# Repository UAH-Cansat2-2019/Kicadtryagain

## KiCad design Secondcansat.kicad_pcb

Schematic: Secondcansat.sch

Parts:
C1, C5: 10uF; C_1206_3216Metric_Pad1.42x1.75mm_HandSolder
C2, C4, C10, C12: 100nF; C_0603_1608Metric_Pad1.05x0.95mm_HandSolder
C3, C14: 5uF; C_0603_1608Metric_Pad1.05x0.95mm_HandSolder
C6: 10uF; C_0805_2012Metric_Pad1.15x1.40mm_HandSolder
C7, C8, C11: 1uF; C_0603_1608Metric_Pad1.05x0.95mm_HandSolder
C9: 50uF; C_1206_3216Metric_Pad1.42x1.75mm_HandSolder
C13: 4.7uF; C_0603_1608Metric_Pad1.05x0.95mm_HandSolder
IC1: XBP9B-XCWT-001; XBP9BXCWT001_2; Mouser Part Number 888-XBP9B-XCWT-001
IMU1: BN0055breakout; BNO055breakout
J1: OpenlogBreakout; PinSocket_1x06_P2.54mm_Vertical
J2: Camera; PinSocket_1x03_P2.54mm_Vertical
J3: Pressure_MS5607; MS5607
J4: Debugger; PinSocket_2x03_P1.27mm_Vertical
J5: SFH_7776_OSRAM; PinSocket_2x04_P2.00mm_Vertical
J6: CAM-M8Q-GPS; CAM-M8Q
J7: GND; PinSocket_1x01_P2.54mm_Vertical
J8: SCL; PinSocket_1x01_P2.54mm_Vertical
J9: 3v; PinSocket_1x01_P2.54mm_Vertical
J10: SDA; PinSocket_1x01_P2.54mm_Vertical
J11: 5V; PinSocket_1x01_P2.54mm_Vertical
J12: Tx; PinSocket_1x01_P2.54mm_Vertical
J13: Rx; PinSocket_1x01_P2.54mm_Vertical
J14: Battery_Holder_keystone 1079; BatteryHolder
L1, L2: 10uH; L_0805_2012Metric_Pad1.15x1.40mm_HandSolder
MCU1: ATxmega128A4U-AU; ATXMEGA128A4U-AU
Moter1, Moter2: Moter_Adafruit_711; PinHeader_2x01_P2.54mm_Vertical
Q1: Q_PMOS_DMG2305UX-13DIDKR-ND; SOT-23
Q2, Q3, Q4: Q_NMOS_BSS138; SOT-23
R1: 274kohm; R_1206_3216Metric
R2: 30Kohm; R_0805_2012Metric_Pad1.15x1.40mm_HandSolder
R3, R4, R5, R6, R7, R11, R12, R13, R14, R15, R16, R17, R20: 10kohm; R_0603_1608Metric_Pad1.05x0.95mm_HandSolder
R8, R10: 2kohm; C_0805_2012Metric
R9: 5kohm; C_0805_2012Metric
R18, R19: 220ohm; R_0603_1608Metric_Pad1.05x0.95mm_HandSolder
Servo1: Servo_Adafruit_1142; PinSocket_1x03_P2.54mm_Vertical
TH1: Therm_NXRT15WB473FA3A016; PinSocket_2x01_P2.54mm_Vertical
U1: VR_TPS7A7001DDAR
U2, U3: H-bridge_MP6513GJ-P; H-Bridge_MP6513GJ-P
VR1: VR__TLV75533PDBVR; VR_296-50411-1-ND
buzzer1: buzzer_MAS803Q; PinSocket_1x02_P2.54mm_Vertical

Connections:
+3V3: C8.2, C9.2, C10.1, C11.1, C14.2, IC1.1, IMU1.1, J1.3, J3.1, J4.2, J5.1, J6.1, J6.9, J9.1, L2.1, R8.2, R11.1, R14.1, R15.1, R16.1, VR1.5
+5V: C6.1, C7.1, J2.2, J11.1, R1.1, R5.1, Servo1.2, U1.6, VR1.1, VR1.3; also elsewhere on the board
+6V: C3.1, Q1.3, R9.2, R17.2, U1.3, U2.5, U3.5, buzzer1.2
ADC_A1: MCU1.41 (PA1), R9.1, R10.2
CSB: J3.4, MCU1.14 (PC4)
GND: C1.2, C2.1, C3.2, C4.1, C5.2, C6.2, C7.2, C8.1, C9.1, C10.2, C11.2, C14.1, IC1.10, IMU1.3, IMU1.6, IMU1.10, J1.1, J1.2, J2.3, J3.2, J3.3, J4.6, J6.4, J6.5, J6.10, J6.11, J6.12, J6.13, J6.14, J6.15, J6.18, J6.19, J6.21, J6.22, J6.27, J6.31, J7.1, J14.3, MCU1.8 (GND), MCU1.18 (GND), MCU1.30 (GND), MCU1.38 (GND), Q1.2, Q2.3, Q3.3, Q4.3, R2.2, R3.2, R4.2, R6.2, R7.1, R10.1, R12.2, R13.2, R20.1, Servo1.1, TH1.1, U1.8, U2.2, U3.2, VR1.2; also elsewhere on the board
INT: J5.7, MCU1.33 (PE3), R14.2
MCUAVCC: C1.1, C2.2, L1.1, MCU1.39 (AVCC)
MCUVCC: C4.2, C5.1, L1.2, L2.2, MCU1.9 (VCC), MCU1.19 (VCC), MCU1.31 (VCC)
MISO: J3.6, MCU1.16 (PC6)
MOSI: J3.7, MCU1.15 (PC5)
MoterRIN1: MCU1.5 (PB1), R3.1, U2.1
MoterRIN2: MCU1.1 (PA5), R12.1, U3.1
MotorFIN1: MCU1.4 (AREFB/PB0), R4.1, U2.3
MotorFIN2: MCU1.44 (PA4), R13.1, U3.3
unnamed: C12.1, C13.1, J5.4
unnamed: C12.2, C13.2, J5.3
unnamed: J2.1, Q4.1
unnamed: J5.5, J5.6
unnamed: J6.16, J6.17
unnamed: J6.25, R18.1
unnamed: J6.26, R19.1
unnamed: J14.1, J14.2
unnamed: J14.4, Q1.1
unnamed 61: J6.8; also elsewhere on the board
unnamed: Moter1.1, U2.6
unnamed: Moter1.2, U2.4
unnamed: Moter2.1, U3.6
unnamed: Moter2.2, U3.4
unnamed: Q2.1, R5.2, Servo1.3
unnamed: Q3.1, buzzer1.1
unnamed: R1.2, R2.1, U1.7
unnamed: R17.1, U1.2
PDICLK: J4.5, MCU1.35 (~RESET~/PDI_CLK), R11.2
PDIDATA: J4.1, MCU1.34 (PDI_DATA)
PWM: MCU1.28 (PE0), Q2.2, R6.1
RX_PD2: IC1.2, MCU1.22 (PD2)
RX_PD6: J13.1, MCU1.26 (PD6), R18.2
SCL: IMU1.5, J5.2, J8.1, MCU1.11 (PC1), R16.2
SCLK: J3.8, MCU1.17 (PC7)
SDA: IMU1.4, J5.8, J10.1, MCU1.10 (PC0), R15.2
TC_PD0: MCU1.20 (PD0), Q3.2, R7.2
TX_PD3: IC1.3, MCU1.23 (PD3)
TX_PD7: J12.1, MCU1.27 (PD7), R19.2
Therm_ADCA0: MCU1.40 (AREFA/PA0), R8.1, TH1.2
USART_RX_PC2: J1.4, MCU1.12 (PC2)
USART_TX_PC3: J1.5, MCU1.13 (PC3)
cameraon: MCU1.32 (PE2), Q4.2, R20.2

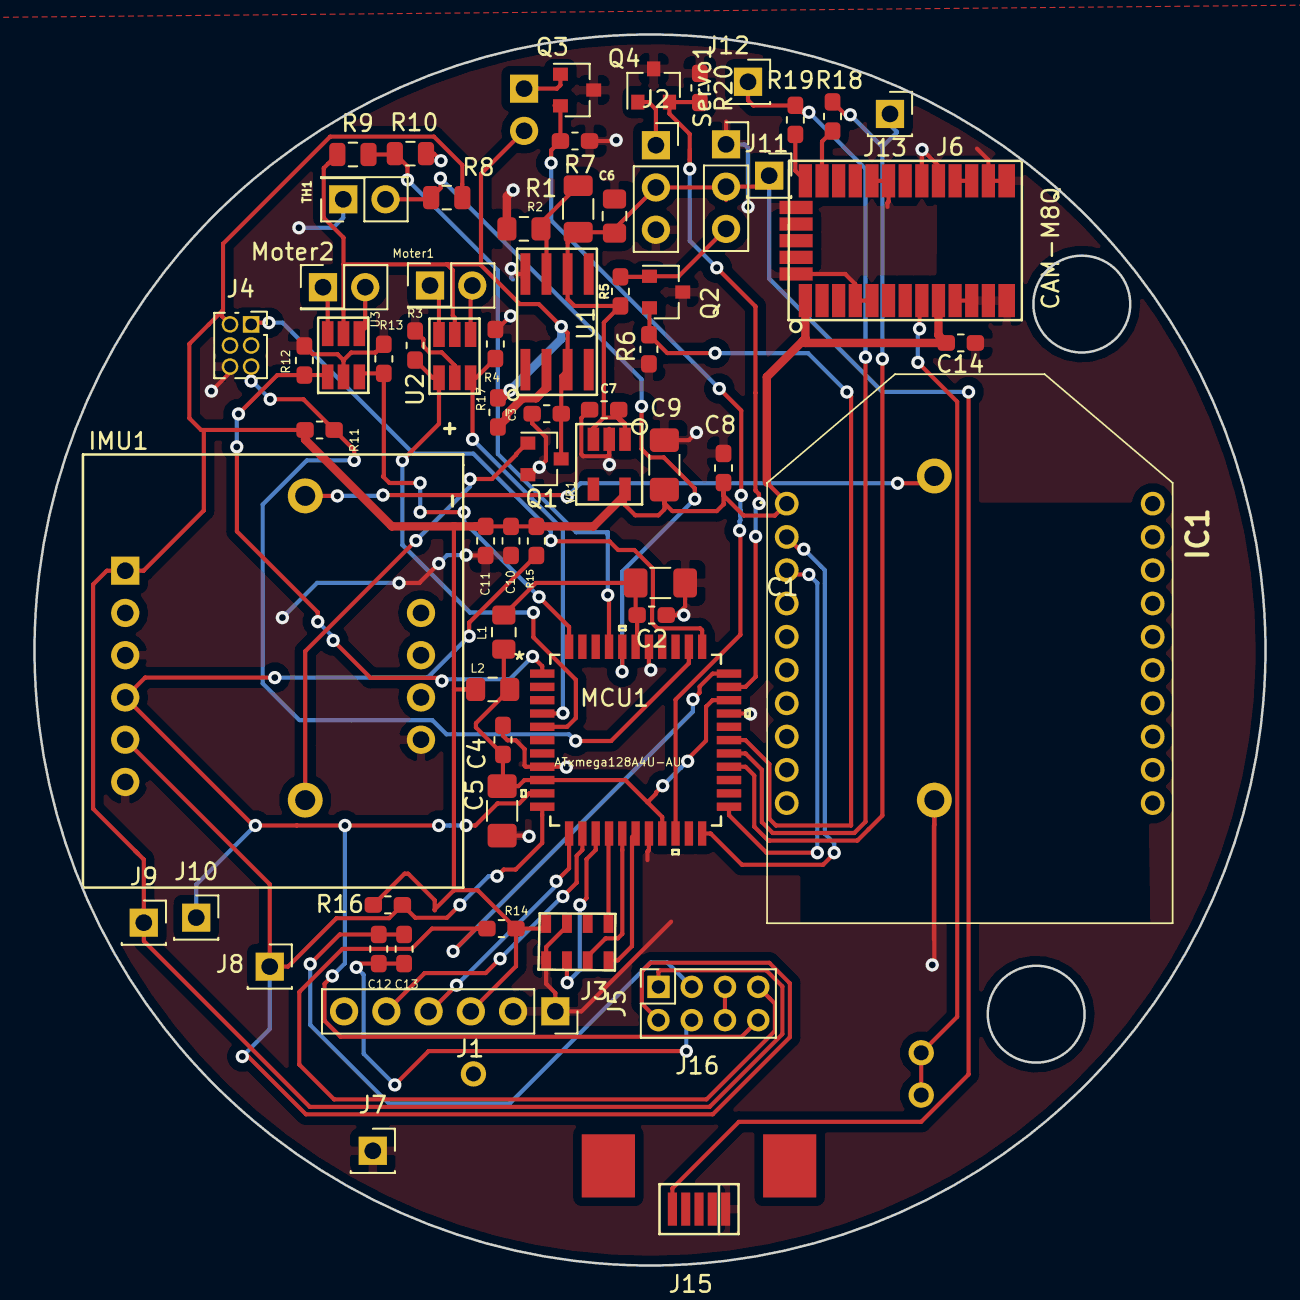
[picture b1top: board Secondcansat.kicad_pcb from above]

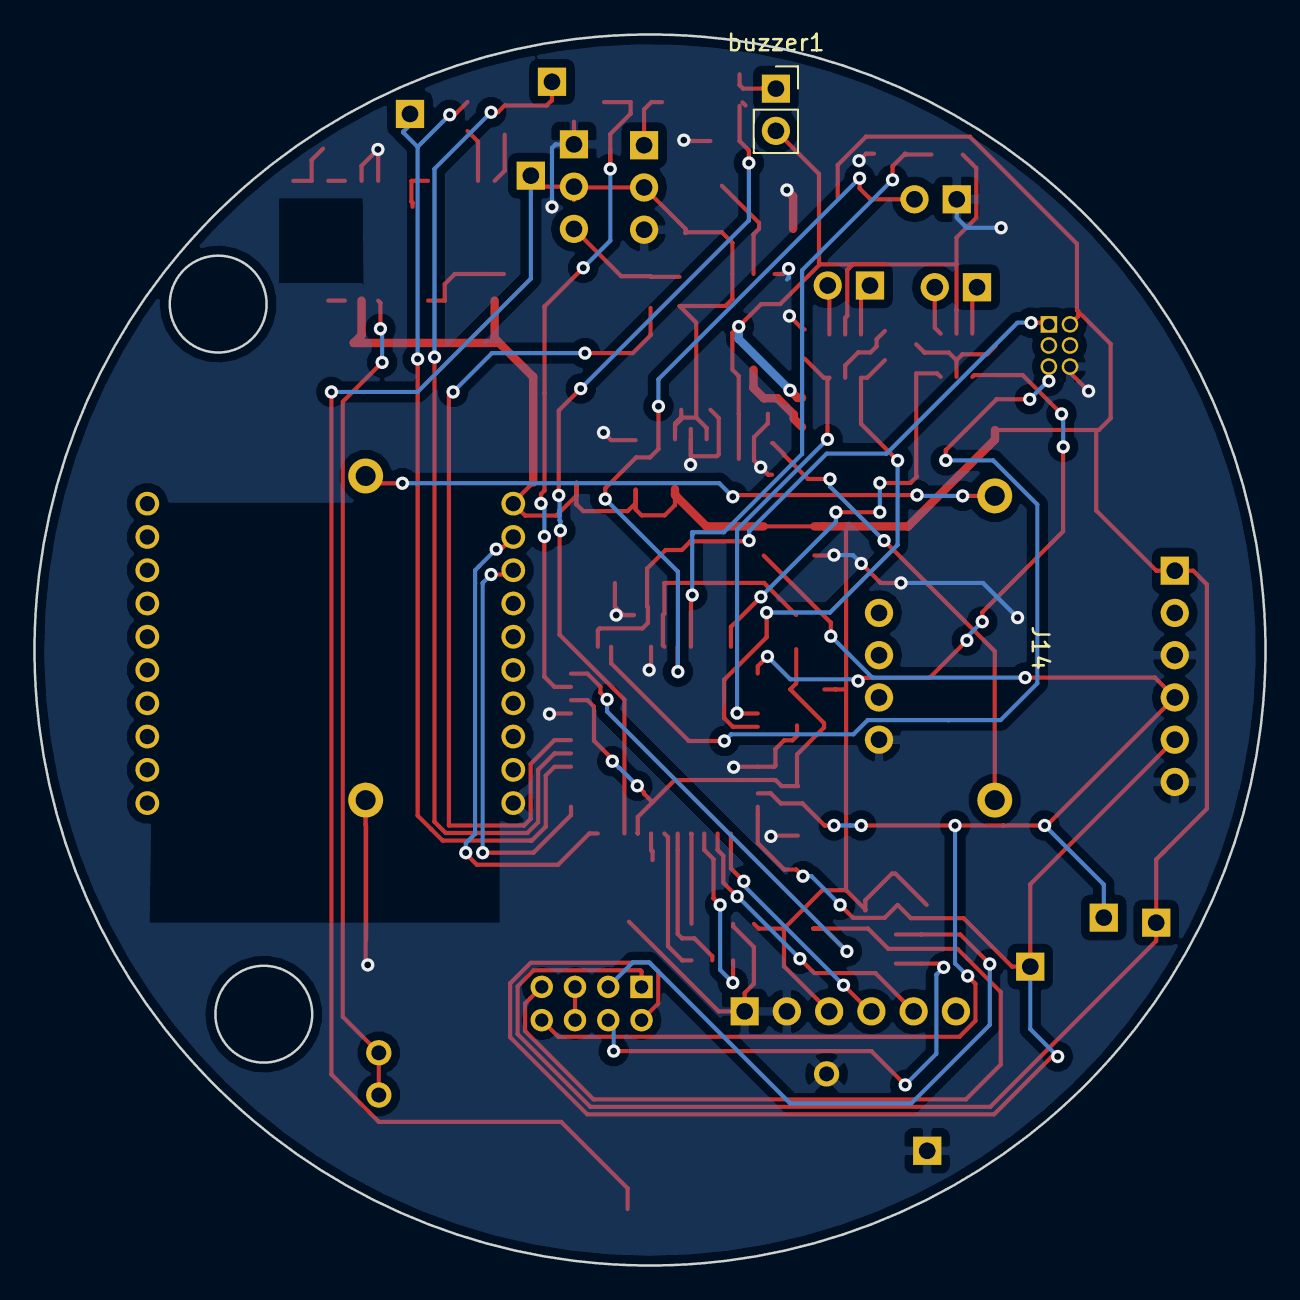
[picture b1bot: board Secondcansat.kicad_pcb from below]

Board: 2 copper layers, 74.0 x 74.0 mm, 68 parts (2 on the bottom side), 48 nets.

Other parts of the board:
J15: USB_B_Mini; USB-Mini
J16: coinBattery; coin_Battery_120591-1

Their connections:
+5V: J15.1; also elsewhere on the board
GND: J15.5, J16.1; also elsewhere on the board
unnamed 61: J16.2, J16.3; also elsewhere on the board

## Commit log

2019-03-09 initialcomit
2019-03-09 footprints moved over
2019-03-09 footprints added
2019-03-09 added everything
2019-03-09 Finish schematic
2019-03-10 fixed schematic and add breakout pcb comp
2019-03-11 made pcb footprints
2019-03-12 Footprint for Cosel 3.3V Reg finished
2019-03-15 Added some part# and fixed H-bridges
2019-03-15 changed schematic symbol
2019-03-16 Added footprints changed some schematic symbols
2019-03-18 Made sugested corrections
2019-03-18 made some footprints
2019-03-19 Did the layout for PCB now Just need to do traces
2019-03-19 Finish PCB
2019-03-20 the real PCB
2019-03-20 moved reference values, added no fill zone and removed extra pin on moter
2019-03-20 added prototype pins
2019-03-24 Made some fixes to the PCB and footprint
2019-03-24 fixed PCB
2019-03-26 added pull down resistors
2019-03-28 changed footprint for Osram
2019-03-29 added backup power and usb mini connector
2019-03-30 Flipped MicroUSB
2019-11-01 Initial comit

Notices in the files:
parts and their libraries:
Copyright 2016 Accelerated Designs. All rights reserved.
